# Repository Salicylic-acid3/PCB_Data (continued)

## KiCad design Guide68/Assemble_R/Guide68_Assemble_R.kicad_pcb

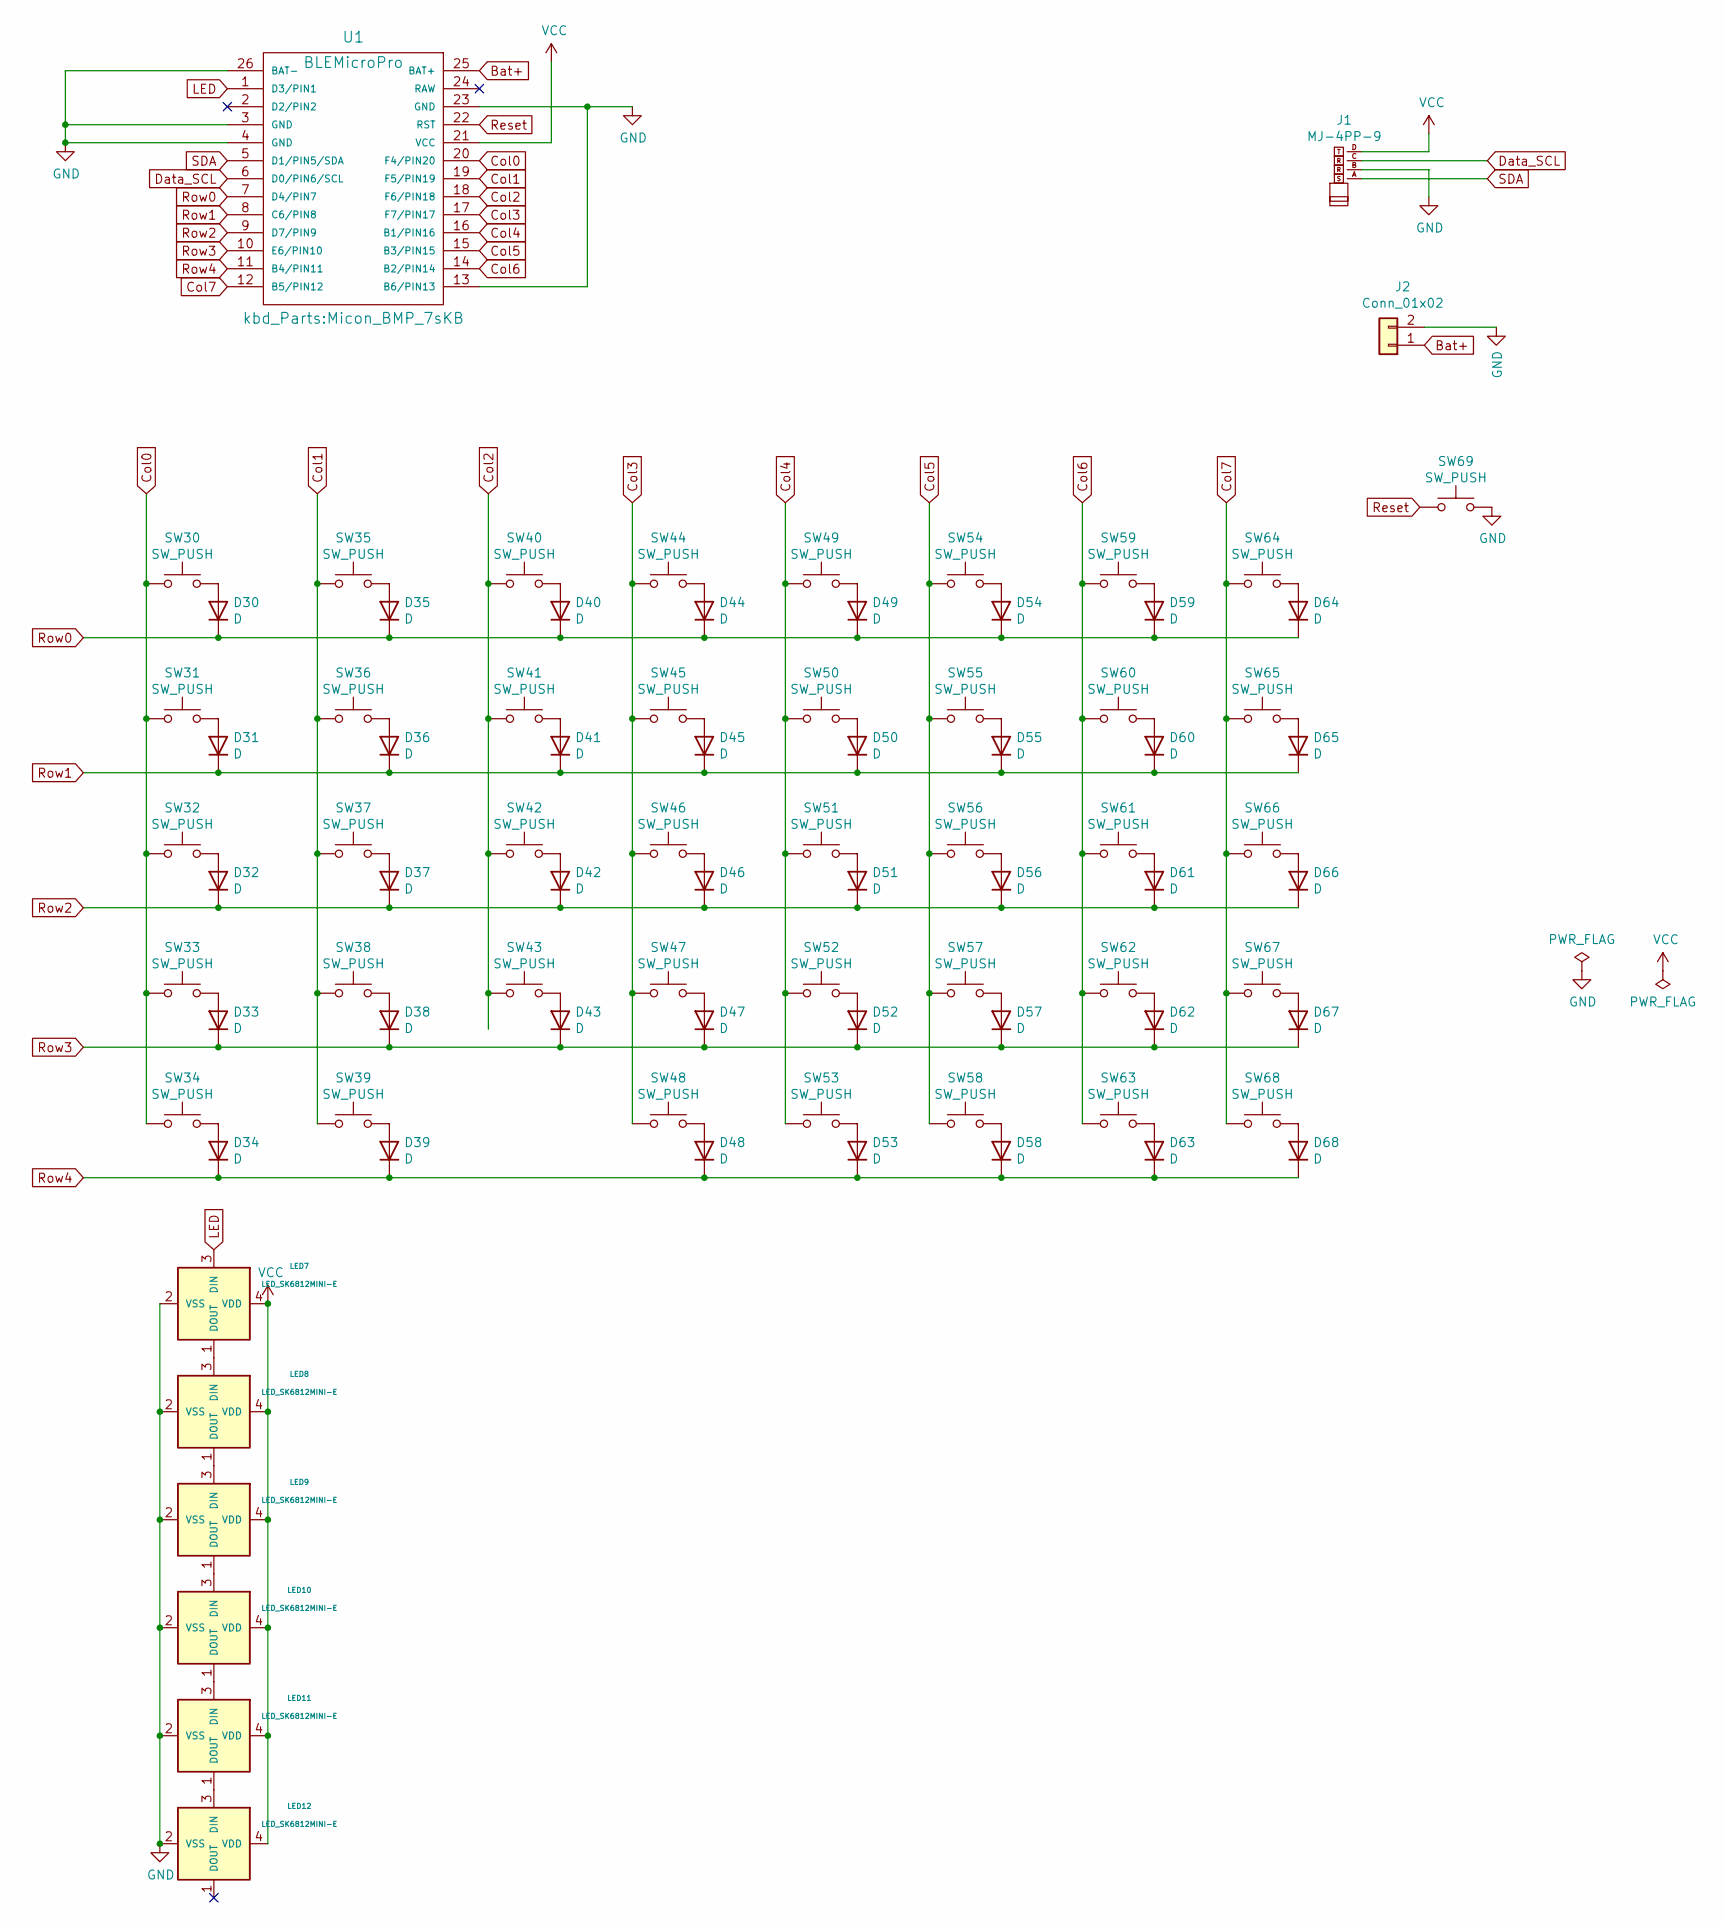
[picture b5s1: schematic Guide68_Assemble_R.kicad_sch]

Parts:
D30, D31, D32, D33, D34, D35, D36, D37, D38, D39, D40, D41, D42, D43, D44, D45, D46, D47, D48, D49, D50, D51, D52, D53, D54, D55, D56, D57, D58, D59, D60, D61, D62, D63, D64, D65, D66, D67, D68: D; Diode_TH_SMD
J1: MJ-4PP-9; TRRS_MJ-4PP-9
J2: Conn_01x02; Battery_BMP_2pin
LED7, LED8, LED9, LED10, LED11, LED12: LED_SK6812MINI-E; LED_SK6812MINI-E_BL
SW30, SW31, SW32, SW33, SW35, SW36, SW37, SW38, SW40, SW41, SW42, SW43, SW44, SW45, SW46, SW47, SW49, SW50, SW51, SW52, SW54, SW55, SW56, SW57, SW58, SW59, SW60, SW62, SW63, SW64, SW65, SW67, SW68: SW_PUSH; CherryMX_Solder_1u
SW34, SW66: SW_PUSH; CherryMX_Solder_1.5u
SW39, SW48, SW53: SW_PUSH; CherryMX_Solder_1.25u
SW61: SW_PUSH; CherryMX_Solder_2.25u_Rev
SW69: SW_PUSH; ResetSW
U1: BLEMicroPro; Micon_BMP_7sKB

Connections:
Bat+: J2.1, U1.25 (BAT+)
Col0: SW30.1, SW31.1, SW32.1, SW33.1, SW34.1, U1.20 (F4)
Col1: SW35.1, SW36.1, SW37.1, SW38.1, SW39.1, U1.19 (F5)
Col2: SW40.1, SW41.1, SW42.1, SW43.1, U1.18 (F6)
Col3: SW44.1, SW45.1, SW46.1, SW47.1, SW48.1, U1.17 (F7)
Col4: SW49.1, SW50.1, SW51.1, SW52.1, SW53.1, U1.16 (B1)
Col5: SW54.1, SW55.1, SW56.1, SW57.1, SW58.1, U1.15 (B3)
Col6: SW59.1, SW60.1, SW61.1, SW62.1, SW63.1, U1.14 (B2)
Col7: SW64.1, SW65.1, SW66.1, SW67.1, SW68.1, U1.12 (B5)
Data_SCL: J1.C, U1.6 (SCL)
GND: J1.B, J2.2, LED7.2 (VSS), LED8.2 (VSS), LED9.2 (VSS), LED10.2 (VSS), LED11.2 (VSS), LED12.2 (VSS), SW69.2, U1.3 (GND), U1.4 (GND), U1.13 (B6), U1.23 (GND), U1.26 (BAT-); also elsewhere on the board
LED: LED7.3 (DIN), U1.1 (TX); also elsewhere on the board
unnamed: D30.2 (A), SW30.2
unnamed: D31.2 (A), SW31.2
unnamed: D32.2 (A), SW32.2
unnamed: D33.2 (A), SW33.2
unnamed: D34.2 (A), SW34.2
unnamed: D35.2 (A), SW35.2
unnamed: D36.2 (A), SW36.2
unnamed: D37.2 (A), SW37.2
unnamed: D38.2 (A), SW38.2
unnamed: D39.2 (A), SW39.2
unnamed: D40.2 (A), SW40.2
unnamed: D41.2 (A), SW41.2
unnamed: D42.2 (A), SW42.2
unnamed: D43.2 (A), SW43.2
unnamed: D44.2 (A), SW44.2
unnamed: D45.2 (A), SW45.2
unnamed: D46.2 (A), SW46.2
unnamed: D47.2 (A), SW47.2
unnamed: D48.2 (A), SW48.2
unnamed: D49.2 (A), SW49.2
unnamed: D50.2 (A), SW50.2
unnamed: D51.2 (A), SW51.2
unnamed: D52.2 (A), SW52.2
unnamed: D53.2 (A), SW53.2
unnamed: D54.2 (A), SW54.2
unnamed: D55.2 (A), SW55.2
unnamed: D56.2 (A), SW56.2
unnamed: D57.2 (A), SW57.2
unnamed: D58.2 (A), SW58.2
unnamed: D59.2 (A), SW59.2
unnamed: D60.2 (A), SW60.2
unnamed: D61.2 (A), SW61.2
unnamed: D62.2 (A), SW62.2
unnamed: D63.2 (A), SW63.2
unnamed: D64.2 (A), SW64.2
unnamed: D65.2 (A), SW65.2
unnamed: D66.2 (A), SW66.2
unnamed: D67.2 (A), SW67.2
unnamed: D68.2 (A), SW68.2
unnamed 51: LED7.1 (DOUT), LED8.3 (DIN); also elsewhere on the board
unnamed 52: LED8.1 (DOUT), LED9.3 (DIN); also elsewhere on the board
unnamed 53: LED10.1 (DOUT), LED11.3 (DIN); also elsewhere on the board
unnamed 54: LED9.1 (DOUT), LED10.3 (DIN); also elsewhere on the board
unnamed 55: LED11.1 (DOUT), LED12.3 (DIN); also elsewhere on the board
Reset: SW69.1, U1.22 (RST)
Row0: D30.1 (K), D35.1 (K), D40.1 (K), D44.1 (K), D49.1 (K), D54.1 (K), D59.1 (K), D64.1 (K), U1.7 (D4)
Row1: D31.1 (K), D36.1 (K), D41.1 (K), D45.1 (K), D50.1 (K), D55.1 (K), D60.1 (K), D65.1 (K), U1.8 (C6)
Row2: D32.1 (K), D37.1 (K), D42.1 (K), D46.1 (K), D51.1 (K), D56.1 (K), D61.1 (K), D66.1 (K), U1.9 (D7)
Row3: D33.1 (K), D38.1 (K), D43.1 (K), D47.1 (K), D52.1 (K), D57.1 (K), D62.1 (K), D67.1 (K), U1.10 (E6)
Row4: D34.1 (K), D39.1 (K), D48.1 (K), D53.1 (K), D58.1 (K), D63.1 (K), D68.1 (K), U1.11 (B4)
SDA: J1.A, U1.5 (SDA)
VCC: J1.D, LED7.4 (VDD), LED8.4 (VDD), LED9.4 (VDD), LED10.4 (VDD), LED11.4 (VDD), LED12.4 (VDD), U1.21 (VCC); also elsewhere on the board

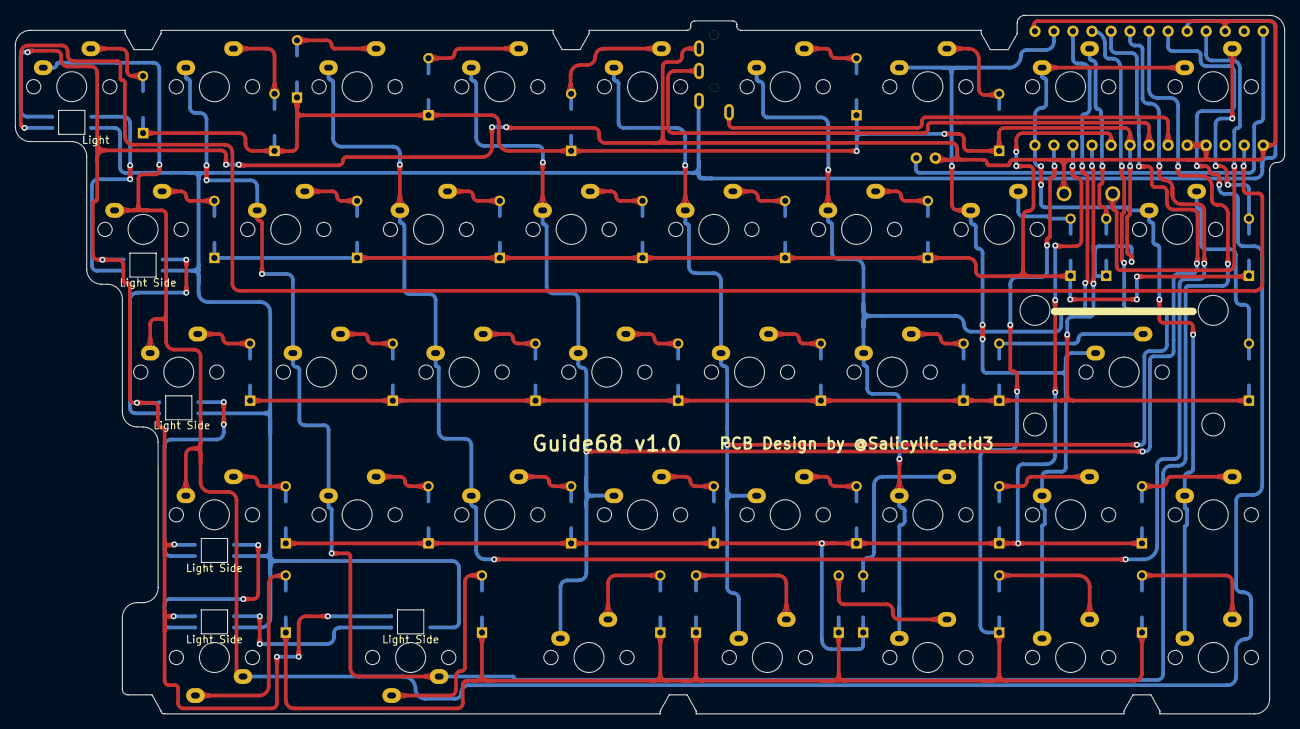
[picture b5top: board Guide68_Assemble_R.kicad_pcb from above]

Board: 2 copper layers, 169.5 x 93.2 mm, 88 parts (1 on the bottom side), 64 nets.

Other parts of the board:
L7, L8, L9, L10, L11, L12: LED_SK6812MINI-E; LED_SK6812MINI-E_BL

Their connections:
GND: L7.2 (VSS), L8.2 (VSS), L9.2 (VSS), L10.2 (VSS), L11.2 (VSS), L12.2 (VSS); also elsewhere on the board
LED: L7.3 (DIN); also elsewhere on the board
unnamed 51: L7.1 (DOUT), L8.3 (DIN); also elsewhere on the board
unnamed 52: L8.1 (DOUT), L9.3 (DIN); also elsewhere on the board
unnamed 53: L10.1 (DOUT), L11.3 (DIN); also elsewhere on the board
unnamed 54: L9.1 (DOUT), L10.3 (DIN); also elsewhere on the board
unnamed 55: L11.1 (DOUT), L12.3 (DIN); also elsewhere on the board
VCC: L7.4 (VDD), L8.4 (VDD), L9.4 (VDD), L10.4 (VDD), L11.4 (VDD), L12.4 (VDD); also elsewhere on the board

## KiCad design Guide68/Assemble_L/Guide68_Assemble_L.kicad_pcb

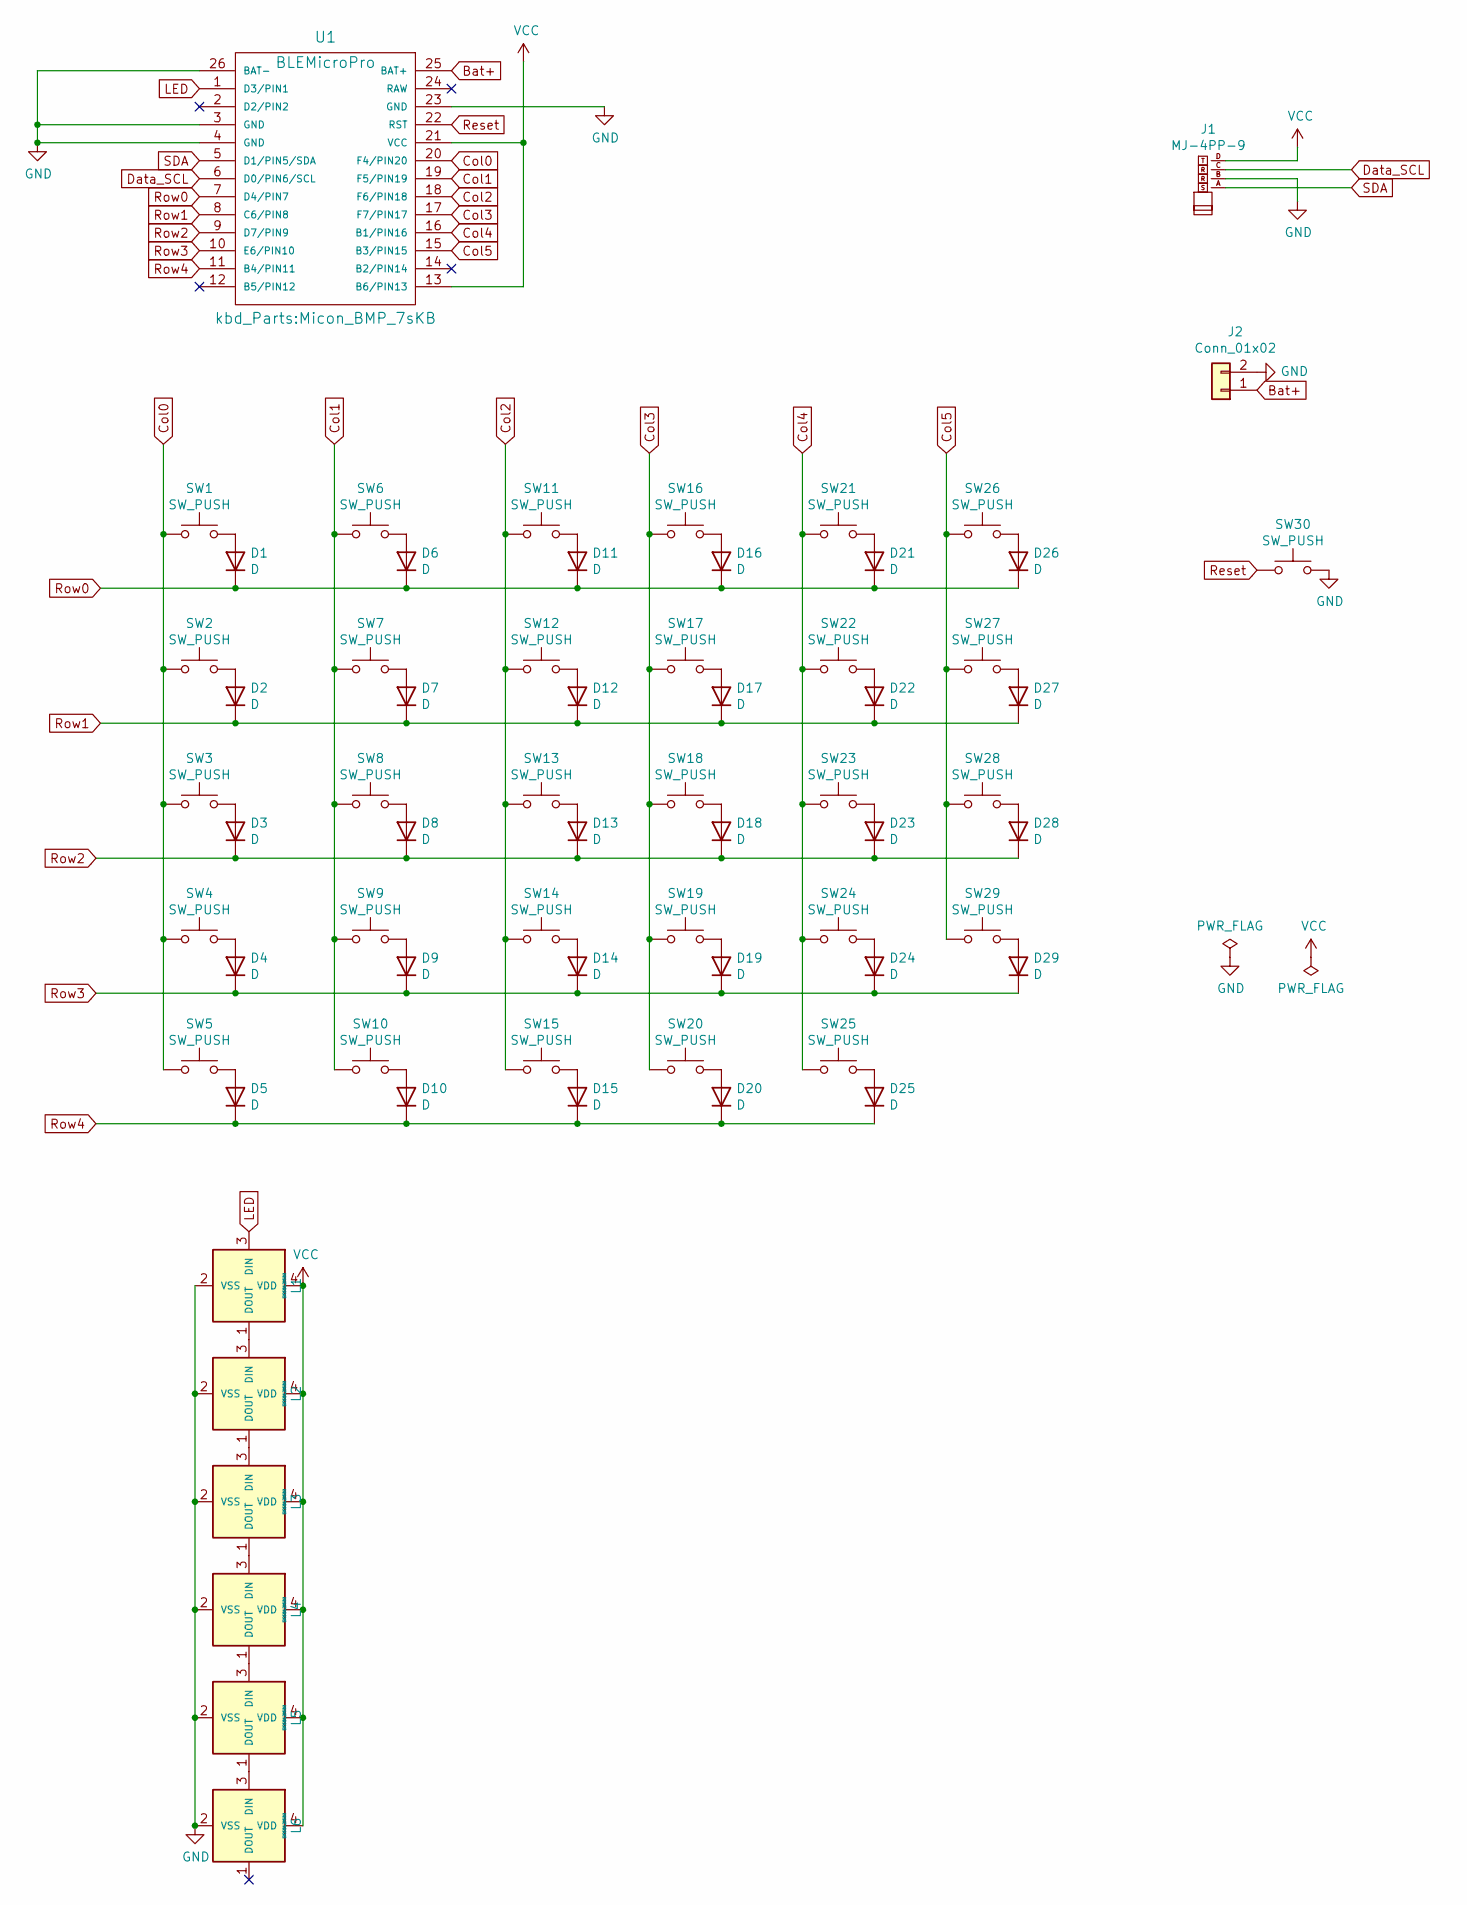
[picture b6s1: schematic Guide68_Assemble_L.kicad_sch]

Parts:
D1, D2, D3, D4, D5, D6, D7, D8, D9, D10, D11, D12, D13, D14, D15, D16, D17, D18, D19, D20, D21, D22, D23, D24, D25, D26, D27, D28, D29: D; Diode_TH_SMD
J1: MJ-4PP-9; TRRS_MJ-4PP-9
J2: Conn_01x02; Battery_BMP_2pin
L1, L2, L3, L4, L5, L6: SK6812MINI; LED_SK6812MINI-E_BL
SW1, SW6, SW7, SW8, SW9, SW11, SW12, SW13, SW14, SW16, SW17, SW18, SW19, SW21, SW22, SW23, SW24, SW26, SW27, SW28, SW29: SW_PUSH; CherryMX_Solder_1u
SW2, SW20, SW25: SW_PUSH; CherryMX_Solder_1.5u
SW3: SW_PUSH; CherryMX_Solder_1.75u
SW4: SW_PUSH; CherryMX_Solder_2u_Rev
SW5, SW10, SW15: SW_PUSH; CherryMX_Solder_1.25u
SW30: SW_PUSH; ResetSW
U1: BLEMicroPro; Micon_BMP_7sKB

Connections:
Bat+: J2.1, U1.25 (BAT+)
Col0: SW1.1, SW2.1, SW3.1, SW4.1, SW5.1, U1.20 (F4/PIN20)
Col1: SW6.1, SW7.1, SW8.1, SW9.1, SW10.1, U1.19 (F5/PIN19)
Col2: SW11.1, SW12.1, SW13.1, SW14.1, SW15.1, U1.18 (F6/PIN18)
Col3: SW16.1, SW17.1, SW18.1, SW19.1, SW20.1, U1.17 (F7/PIN17)
Col4: SW21.1, SW22.1, SW23.1, SW24.1, SW25.1, U1.16 (B1/PIN16)
Col5: SW26.1, SW27.1, SW28.1, SW29.1, U1.15 (B3/PIN15)
Data_SCL: J1.C, U1.6 (D0/PIN6/SCL)
GND: J1.B, J2.2, L1.2 (VSS), L2.2 (VSS), L3.2 (VSS), L4.2 (VSS), L5.2 (VSS), L6.2 (VSS), SW30.2, U1.3 (GND), U1.4 (GND), U1.23 (GND), U1.26 (BAT-)
LED: L1.3 (DIN), U1.1 (D3/PIN1)
unnamed: D1.2 (A), SW1.2
unnamed: D2.2 (A), SW2.2
unnamed: D3.2 (A), SW3.2
unnamed: D4.2 (A), SW4.2
unnamed: D5.2 (A), SW5.2
unnamed: D6.2 (A), SW6.2
unnamed: D7.2 (A), SW7.2
unnamed: D8.2 (A), SW8.2
unnamed: D9.2 (A), SW9.2
unnamed: D10.2 (A), SW10.2
unnamed: D11.2 (A), SW11.2
unnamed: D12.2 (A), SW12.2
unnamed: D13.2 (A), SW13.2
unnamed: D14.2 (A), SW14.2
unnamed: D15.2 (A), SW15.2
unnamed: D16.2 (A), SW16.2
unnamed: D17.2 (A), SW17.2
unnamed: D18.2 (A), SW18.2
unnamed: D19.2 (A), SW19.2
unnamed: D20.2 (A), SW20.2
unnamed: D21.2 (A), SW21.2
unnamed: D22.2 (A), SW22.2
unnamed: D23.2 (A), SW23.2
unnamed: D24.2 (A), SW24.2
unnamed: D25.2 (A), SW25.2
unnamed: D26.2 (A), SW26.2
unnamed: D27.2 (A), SW27.2
unnamed: D28.2 (A), SW28.2
unnamed: D29.2 (A), SW29.2
unnamed: L1.1 (DOUT), L2.3 (DIN)
unnamed: L2.1 (DOUT), L3.3 (DIN)
unnamed: L3.1 (DOUT), L4.3 (DIN)
unnamed: L4.1 (DOUT), L5.3 (DIN)
unnamed: L5.1 (DOUT), L6.3 (DIN)
Reset: SW30.1, U1.22 (RST)
Row0: D1.1 (K), D6.1 (K), D11.1 (K), D16.1 (K), D21.1 (K), D26.1 (K), U1.7 (D4/PIN7)
Row1: D2.1 (K), D7.1 (K), D12.1 (K), D17.1 (K), D22.1 (K), D27.1 (K), U1.8 (C6/PIN8)
Row2: D3.1 (K), D8.1 (K), D13.1 (K), D18.1 (K), D23.1 (K), D28.1 (K), U1.9 (D7/PIN9)
Row3: D4.1 (K), D9.1 (K), D14.1 (K), D19.1 (K), D24.1 (K), D29.1 (K), U1.10 (E6/PIN10)
Row4: D5.1 (K), D10.1 (K), D15.1 (K), D20.1 (K), D25.1 (K), U1.11 (B4/PIN11)
SDA: J1.A, U1.5 (D1/PIN5/SDA)
VCC: J1.D, L1.4 (VDD), L2.4 (VDD), L3.4 (VDD), L4.4 (VDD), L5.4 (VDD), L6.4 (VDD), U1.13 (B6/PIN13), U1.21 (VCC)

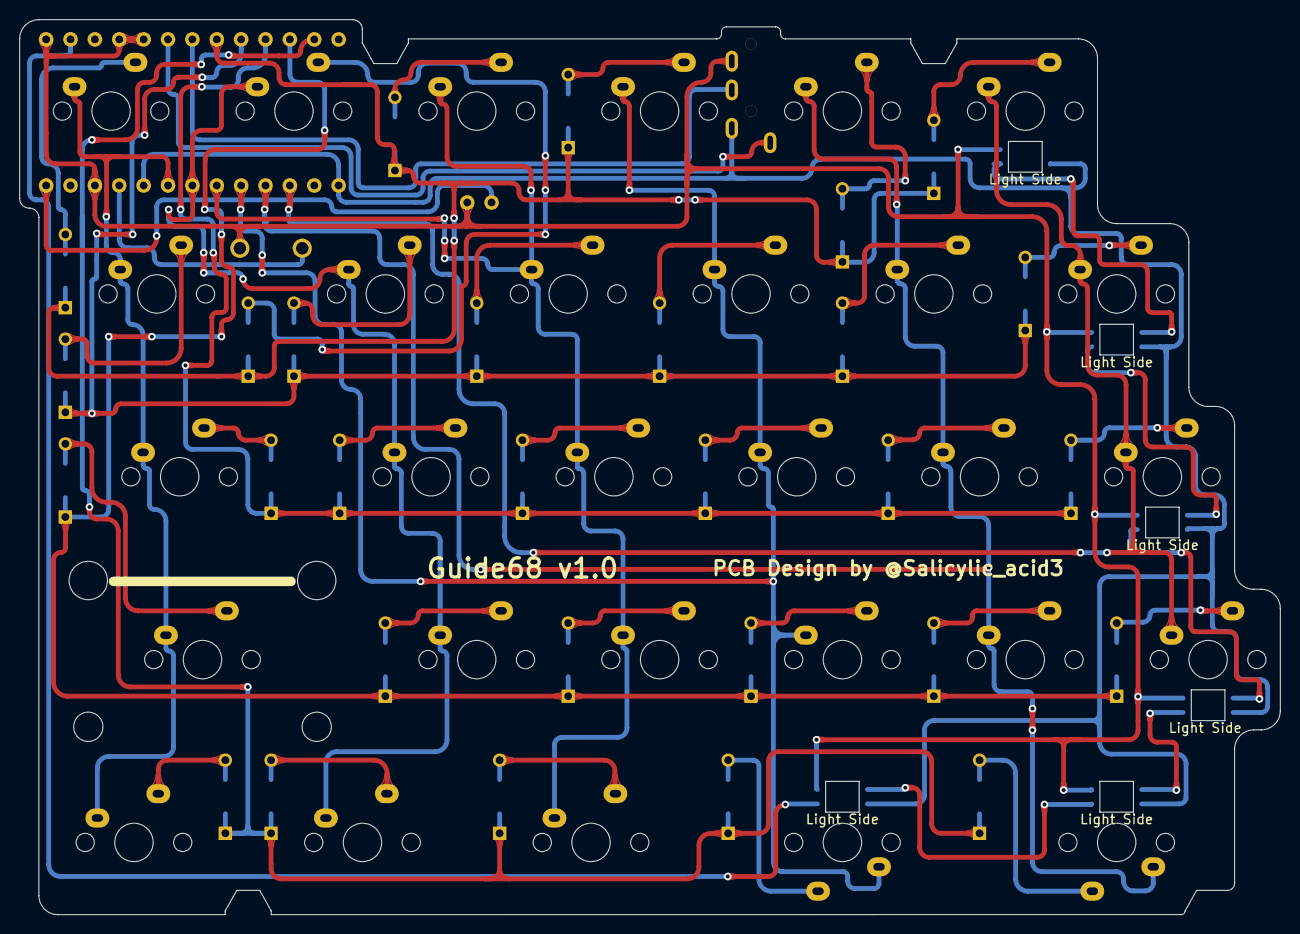
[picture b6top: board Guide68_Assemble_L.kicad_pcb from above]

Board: 2 copper layers, 131.3 x 93.2 mm, 68 parts (1 on the bottom side), 52 nets.

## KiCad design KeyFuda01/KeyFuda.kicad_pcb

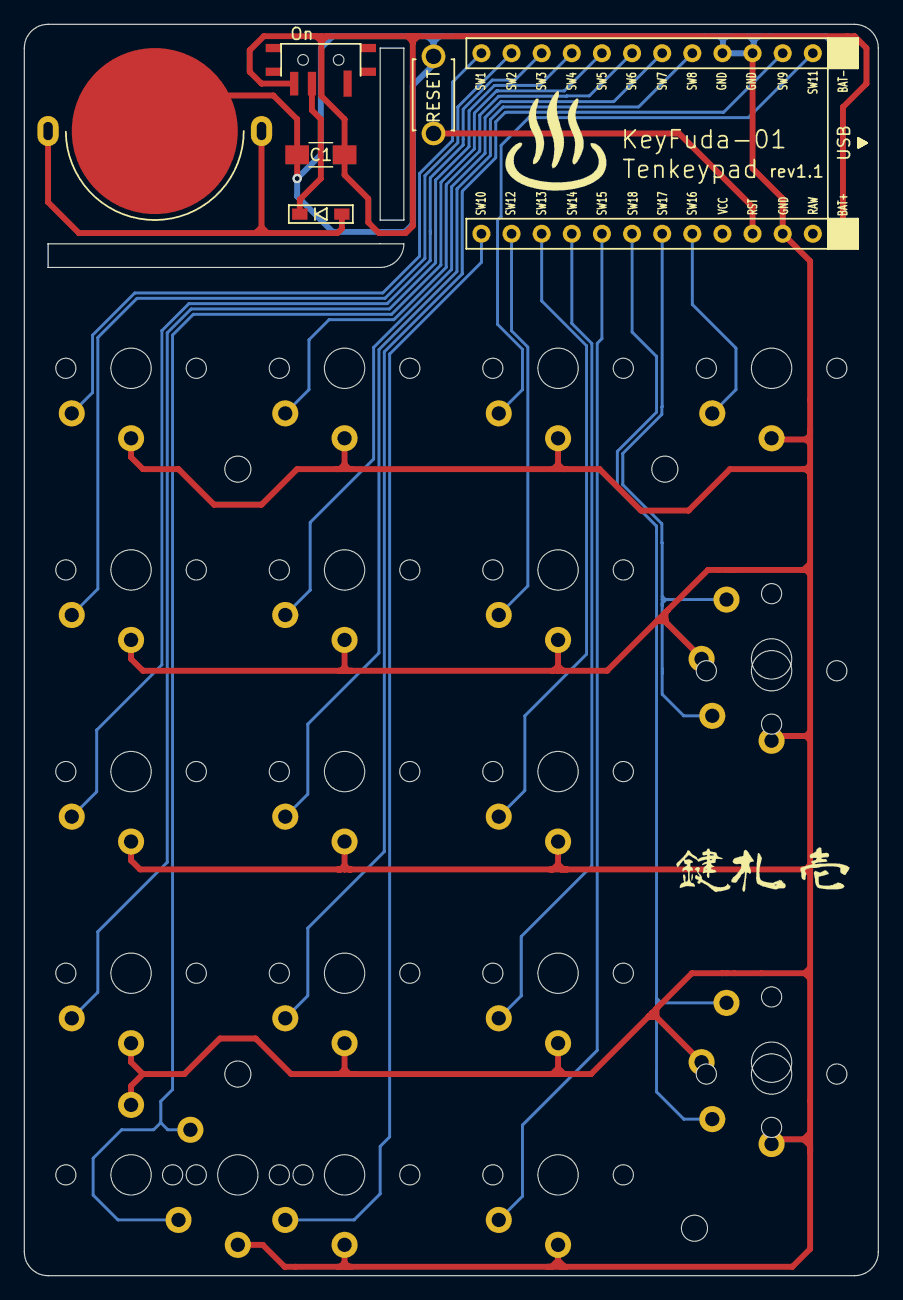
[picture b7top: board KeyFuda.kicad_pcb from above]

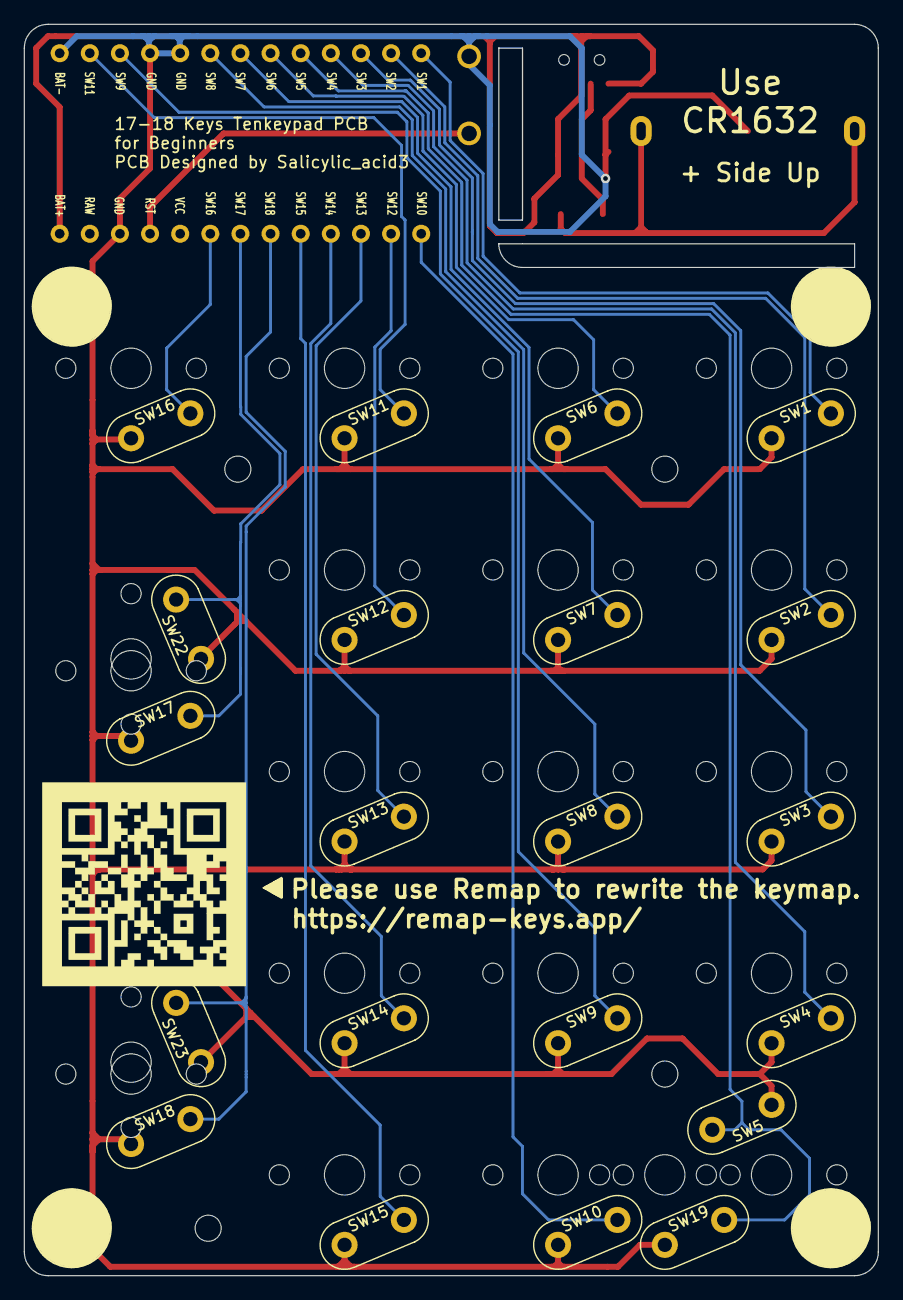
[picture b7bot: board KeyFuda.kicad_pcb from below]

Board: 2 copper layers, 72.0 x 105.5 mm, 31 parts (2 on the bottom side), 23 nets.

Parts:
BT1: Battery_Cell; Battery_ali_CR1632
C1: C; Capacitor_1206
D1: D; Diode_SMD
Ref**: Val**; m2_Screw_Hole
Ref**#2, Ref**#3, Ref**#4: Val**; m2_Screw_Hole
SW1, SW2, SW3, SW4, SW5, SW6, SW7, SW8, SW9, SW10, SW11, SW12, SW13, SW14, SW15, SW16, SW17, SW18, SW19, SW22, SW23: SW_PUSH; Choc_v1_solder
SW20: SW_PUSH; ResetSW
SW21: SW_Push_SPDT; TGSW_MK12C02
U1: Micon_BLEMicroPro; Micon_BMP_7sKB

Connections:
Bat+: C1.1, SW21.3, U1.25
GND: BT1.2, C1.2, SW1.2, SW2.2, SW3.2, SW4.2, SW5.2, SW6.2, SW7.2, SW8.2, SW9.2, SW10.2, SW11.2, SW12.2, SW13.2, SW14.2, SW15.2, SW16.2, SW17.2, SW18.2, SW19.2, SW20.2, SW22.2, SW23.2, U1.3, U1.4, U1.23, U1.26
unnamed: BT1.1, D1.2
unnamed: D1.1, SW21.2
Reset: SW20.1, U1.22
SW1: SW1.1, U1.12
SW2: SW2.1, U1.11
SW3: SW3.1, U1.10
SW4: SW4.1, U1.9
SW5: SW5.1, SW19.1, U1.8
SW6: SW6.1, U1.7
SW7: SW7.1, U1.6
SW8: SW8.1, U1.5
SW9: SW9.1, U1.2
SW10: SW10.1, U1.13
SW11: SW11.1, U1.1
SW12: SW12.1, U1.14
SW13: SW13.1, U1.15
SW14: SW14.1, U1.16
SW15: SW15.1, U1.17
SW16: SW16.1, U1.20
SW17: SW17.1, SW22.1, U1.19
SW18: SW18.1, SW23.1, U1.18

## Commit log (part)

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2019-08-15 Naked60 PCB Data Add
2021-03-05 キーボード設計ファイル、ガーバーファイルの追加
    以下のキーボードの設計ファイル、ガーバーファイルの追加
    ・Nafuda
    ・Setta21
    ・Getta25
    ・Kleine Gherkin
2022-08-17 KeyFuda01の追加
2022-10-05 Trayの3Dデータを追加
2022-12-21 Guide68の追加
2022-12-21 スイッチ穴を更新
2023-10-23 J67Gの追加
2024-04-22 7Nanoを追加
2024-04-22 AJisai74を追加
2024-07-14 GoForty系のテンプレートを追加
2024-08-09 KeebMicro-Cを追加
2024-08-09 Readmeの追加
